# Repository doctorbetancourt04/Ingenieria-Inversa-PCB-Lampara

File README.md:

# Ingenieria Inversa PCB Lampara
Mini-proyecto de Ingeniería Inversa de la PCB del bombillo LED de Tecnolite modelo 50LHBLEDT65MV200.

## Autoría

Este proyecto es de **Mario Betancourt**, y este repositorio se publica desde su cuenta
personal de GitHub.

Los primeros commits aparecen con el autor `mariobet23440`, que es su cuenta
estudiantil. Es la misma persona: se usó esa cuenta por error en la configuración
de git. Todo el contenido pertenece al mismo autor y se distribuye bajo la licencia
del archivo `LICENSE` (GPL-3.0).

Parte del trabajo se hizo con asistencia de IA; el detalle está en
[`prompts/bitacora_prompts.md`](prompts/bitacora_prompts.md).

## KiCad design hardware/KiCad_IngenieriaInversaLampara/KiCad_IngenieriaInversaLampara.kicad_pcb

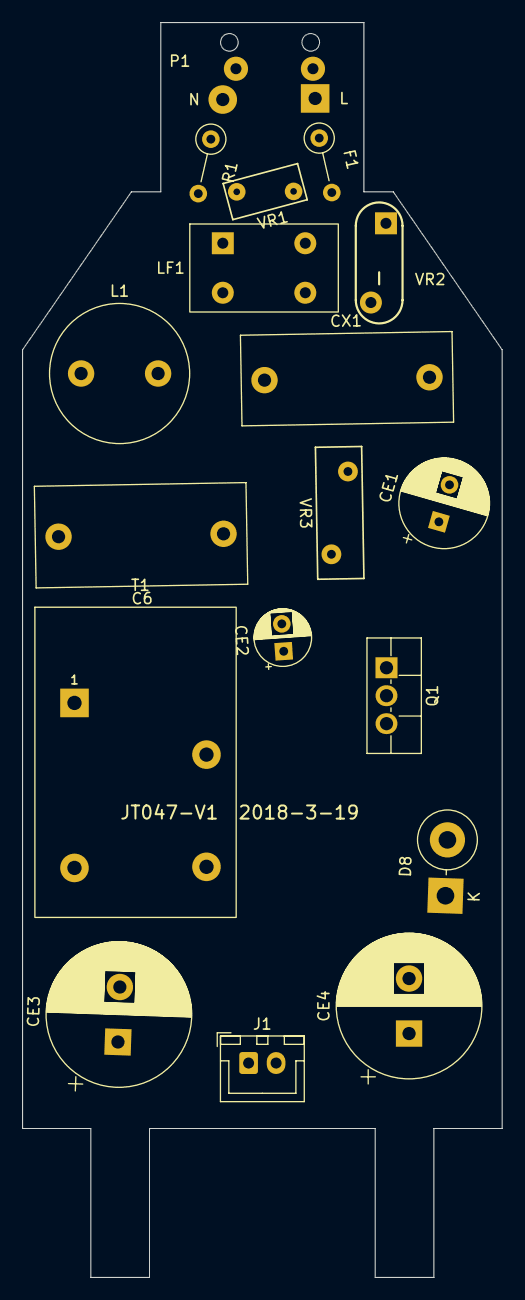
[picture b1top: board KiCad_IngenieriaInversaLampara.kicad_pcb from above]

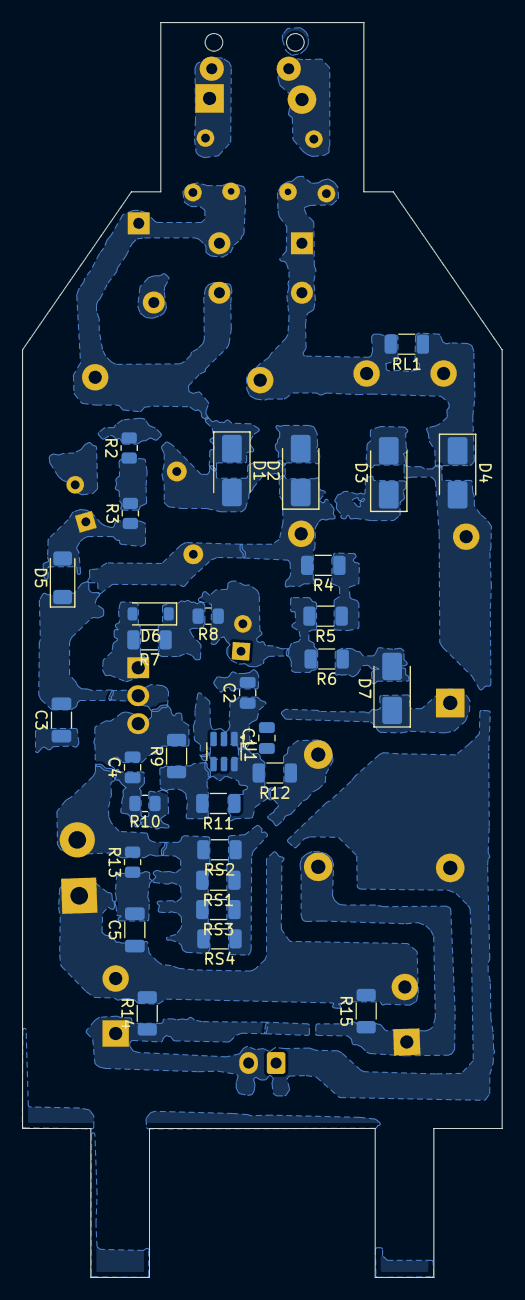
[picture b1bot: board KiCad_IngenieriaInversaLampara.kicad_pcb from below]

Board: 2 copper layers, 43.6 x 114.1 mm, 50 parts (32 on the bottom side), 27 nets, no tracks yet.

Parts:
C1: (no montado); C_0805_2012Metric
C2, C4: ? (MLCC); C_0805_2012Metric
C3, C5: (no montado); C_1206_3216Metric
C6: CBB ?; C_Rect_L19.0mm_W9.0mm_P15.00mm_MKS4
CE1: CE (no montado); CP_Radial_D8.0mm_P3.50mm
CE2: 10uF 50V; CP_Radial_D5.0mm_P2.50mm
CE3, CE4: 270uF 100V; CP_Radial_D13.0mm_P5.00mm
CX1: X2 (no montado); C_Rect_L19.0mm_W8.0mm_P15.00mm_MKS4
D1, D2, D3, D4: M7 ?; D_SMA
D5: (no montado); D_MiniMELF
D6: 1N4148W ? (T4); D_SOD-123
D7: ?; D_SMA
D8: Diodo rápido ?; D_DO-201AD_P5.08mm_Vertical_KathodeUp
F1: Fusible ?; R_Axial_DIN0207_L6.3mm_D2.5mm_P5.08mm_Vertical
J1: LED (- , +); JST_XH_B2B-XH-A_1x02_P2.50mm_Vertical
L1: L (no montado); L_Radial_D12.5mm_P7.00mm_Fastron_09HCP
LF1: CMC (no montado); LF1_CMC_4pin_7.5x4.5mm
P1: AC 120V (L, N); P1_Entrada_AC_Cables
Q1: FIR12N65F; TO-220F-3_Vertical
R1: R fusible ?; R_Axial_DIN0207_L6.3mm_D2.5mm_P5.08mm_Vertical
R2, R3, R13: (no montado); R_0805_2012Metric
R4, R5: 330k (334); R_1206_3216Metric
R6, R7: 22 (220); R_1206_3216Metric
R8: 75k (753); R_0805_2012Metric
R9: 12k (123); R_1206_3216Metric
R10: 560 (561); R_0805_2012Metric
R11: 68k (683); R_1206_3216Metric
R12: 0; R_1206_3216Metric
R14: 75k (753); R_1206_3216Metric
R15: (no montado); R_1206_3216Metric
RL1: (no montado); R_1206_3216Metric
RS1, RS2, RS3: 1.2 (1R20); R_1206_3216Metric
RS4: 1.3 (1R30); R_1206_3216Metric
T1: Transformador EE ?; T1_EE_4pin
U1: H0TN 9L99 ? (flyback); SOT-23-6
VR1: MOV ?; RV_Disc_D7mm_W3.4mm_P5mm
VR2: MOV (no montado); VR2_Ovalo_P7.5mm
VR3: MOV ?; RV_Disc_D12mm_W4.2mm_P7.5mm

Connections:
/AC_L: CX1.2, D1.1, D2.2 (A), F1.2, LF1.3, LF1.4, VR1.2, VR2.1
/AC_L_ENTRADA: F1.1, P1.1
/AC_N: CX1.1, D3.2 (A), D4.1, L1.1, L1.2, LF1.1, LF1.2, R1.2, RL1.1, RL1.2, VR1.1, VR2.2
/AC_N_ENTRADA: P1.2, R1.1
/AUX_T1: D7.1 (K), T1.1 (AA)
/COMPUERTA_CI: D6.1 (K), R7.1, R8.2, U1.3
/COMPUERTA_Q1: D6.2 (A), Q1.1 (G), R7.2
/CS: R10.1, U1.5
/DC+: C3.1, C6.1, D2.1 (K), D3.1 (K), R4.2, VR3.2
/DC-: C6.2, D1.2, D4.2, VR3.1
/FB: R9.1, R11.2, U1.4
/GND_CI: CE2.2, R8.1, U1.2
/LED+: CE3.1, CE4.1, J1.2, R14.1, R15.1, T1.2 (AB), T1.4 (SB)
/LED-: C5.1, CE3.2, CE4.2, D8.1 (K), J1.1, R14.2, R15.2
/RS_A: RS1.1, RS2.1, RS3.1, RS4.1
/RS_B: RS1.2, RS2.2, RS3.2, RS4.2
/U1_PIN6: C4.2, Q1.3 (S), R9.2, R12.2, U1.6
/VCC: C2.1, CE2.1, R5.2, R6.2, U1.1
unnamed: C4.1, R10.2
unnamed: C5.2, R13.1
unnamed: CE1.1, D5.2 (A), R3.1
unnamed: C3.2, D5.1 (K)
unnamed: D7.2 (A), R6.1
unnamed: D8.2 (A), R13.2
unnamed: R2.1, R3.2
unnamed: R4.1, R5.1
unnamed: R12.1, T1.3 (SA)
